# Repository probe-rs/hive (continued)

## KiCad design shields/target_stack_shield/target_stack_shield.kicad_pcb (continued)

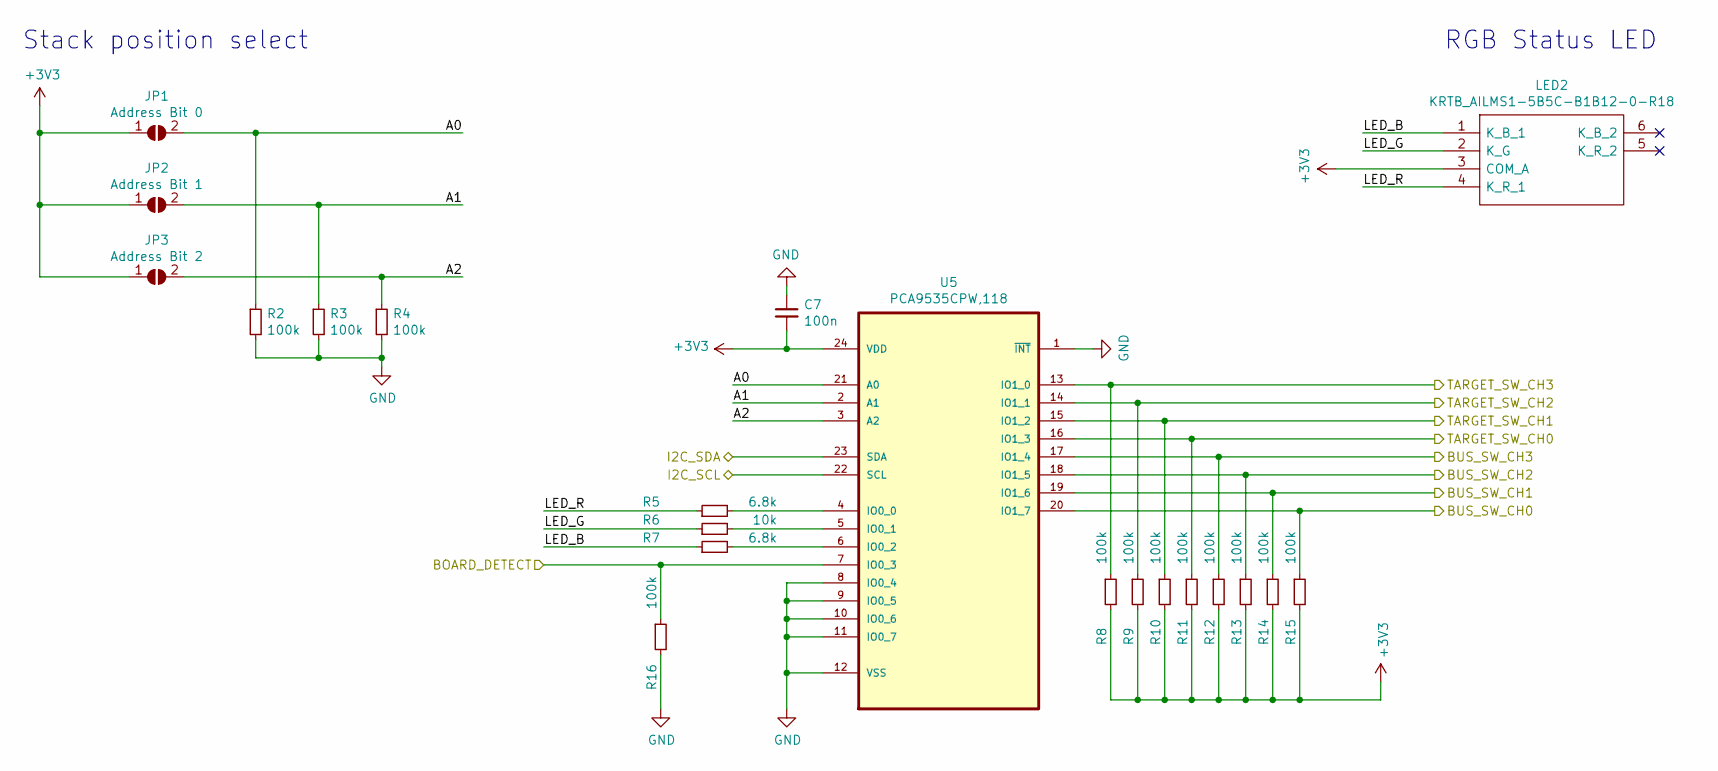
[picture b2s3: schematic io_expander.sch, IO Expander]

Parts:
C7: 100n; C_0603_1608Metric_Pad1.05x0.95mm_HandSolder
JP1: Address Bit 0; SolderJumper-2_P1.3mm_Open_TrianglePad1.0x1.5mm
JP2: Address Bit 1; SolderJumper-2_P1.3mm_Open_TrianglePad1.0x1.5mm
JP3: Address Bit 2; SolderJumper-2_P1.3mm_Open_TrianglePad1.0x1.5mm
LED2: KRTB_AILMS1-5B5C-B1B12-0-R18; KRTBAILMS15B5CB1B120R18; Mouser Part Number 720-KRTBAILMS1A2872
R2, R3, R4, R8, R9, R10, R11, R12, R13, R14, R15, R16: 100k; R_0603_1608Metric_Pad1.05x0.95mm_HandSolder
R5, R7: 6.8k; R_0603_1608Metric_Pad1.05x0.95mm_HandSolder
R6: 10k; R_0603_1608Metric_Pad1.05x0.95mm_HandSolder
U5: PCA9535CPW,118; SOP65P640X110-24N; MPN PCA9535CPW,118; Digikey Price (CHF) 1.9

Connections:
/BOARD_DETECT: R16.1, U5.7 (IO0_3); also elsewhere on the board
/Bus switches/BUS_SW_CH0: R15.1, U5.20 (IO1_7); also elsewhere on the board
/Bus switches/BUS_SW_CH1: R14.1, U5.19 (IO1_6); also elsewhere on the board
/Bus switches/BUS_SW_CH2: R13.1, U5.18 (IO1_5); also elsewhere on the board
/Bus switches/BUS_SW_CH3: R12.1, U5.17 (IO1_4); also elsewhere on the board
/Bus switches/IO Expander/A0: JP1.2 (B), R2.1, U5.21 (A0)
/Bus switches/IO Expander/A1: JP2.2 (B), R3.1, U5.2 (A1)
/Bus switches/IO Expander/A2: JP3.2 (B), R4.1, U5.3 (A2)
/Bus switches/IO Expander/LED_B: LED2.1 (K_B_1), R7.1
/Bus switches/IO Expander/LED_G: LED2.2 (K_G), R6.1
/Bus switches/IO Expander/LED_R: LED2.4 (K_R_1), R5.1
/Bus switches/TARGET_SW_CH0: R11.1, U5.16 (IO1_3); also elsewhere on the board
/Bus switches/TARGET_SW_CH1: R10.1, U5.15 (IO1_2); also elsewhere on the board
/Bus switches/TARGET_SW_CH2: R9.1, U5.14 (IO1_1); also elsewhere on the board
/Bus switches/TARGET_SW_CH3: R8.1, U5.13 (IO1_0); also elsewhere on the board
/I2C_SCL: U5.22 (SCL); also elsewhere on the board
/I2C_SDA: U5.23 (SDA); also elsewhere on the board
GND: C7.1, R2.2, R3.2, R4.2, R16.2, U5.1 (~INT), U5.8 (IO0_4), U5.9 (IO0_5), U5.10 (IO0_6), U5.11 (IO0_7), U5.12 (VSS); also elsewhere on the board
unnamed: R5.2, U5.4 (IO0_0)
unnamed: R6.2, U5.5 (IO0_1)
unnamed: R7.2, U5.6 (IO0_2)

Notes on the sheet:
Stack position select
RGB Status LED

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
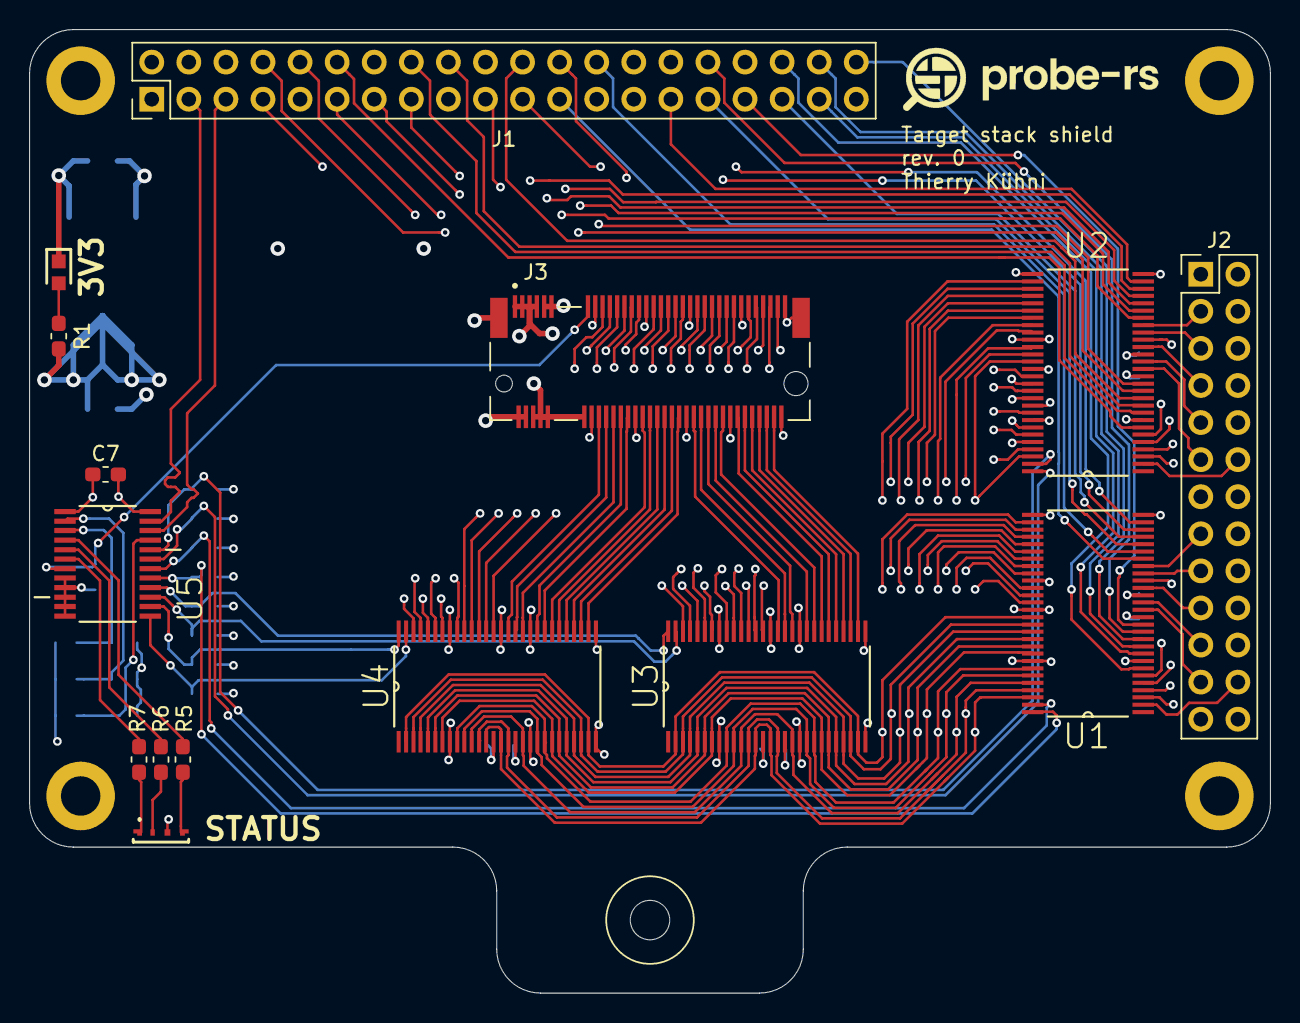
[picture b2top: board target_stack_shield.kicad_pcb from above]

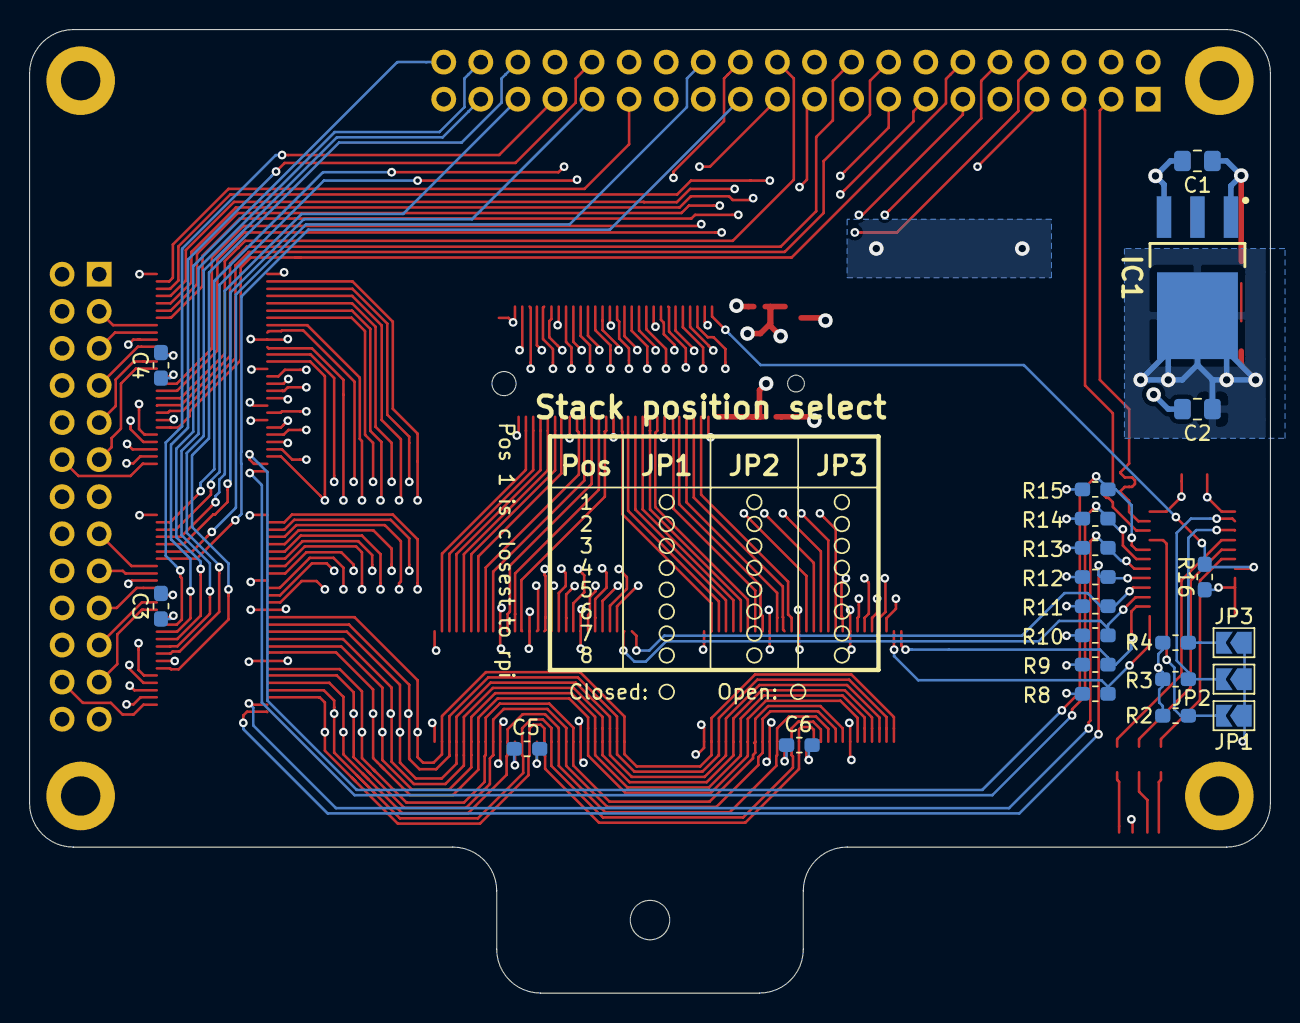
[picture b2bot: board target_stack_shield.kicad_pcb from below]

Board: 4 copper layers, 85.0 x 66.0 mm, 42 parts (22 on the bottom side), 123 nets.

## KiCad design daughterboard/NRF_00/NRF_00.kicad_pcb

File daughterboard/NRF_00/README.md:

## Daughterboard NRF_00
This Daughterboard features several nRF MCUs.

### Targets
The following targets are implemented on this Daughterboard:
| Designation | MCU |
| --- | --- |
| target0 | BT40E (nRF5340) |
| target1 | NRF52832-QFAB-T |
| target2 | NRF52840-DONGLE |
| target3 | NRF51822-QFAC-R7 |

### Partlist
The partlist for this Daughterboard is available [here](https://octopart.com/bom-tool/1QN2uwwk).

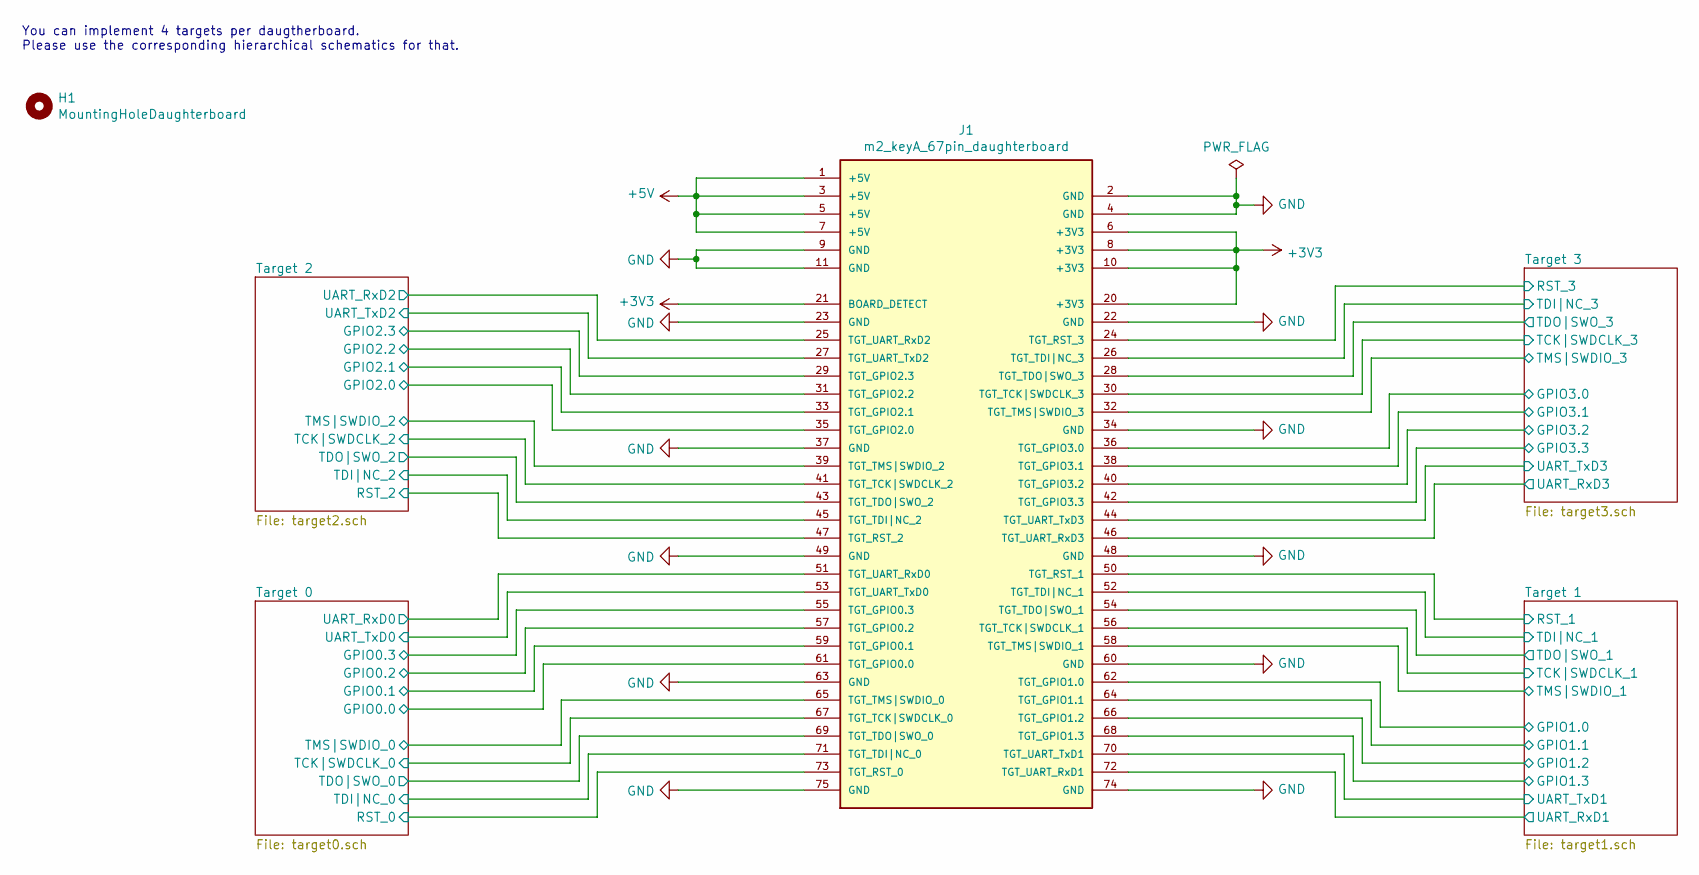
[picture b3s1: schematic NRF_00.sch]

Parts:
H1: MountingHoleDaughterboard; MountingHole_2.7mm_M2.5
J1: m2_keyA_67pin_daughterboard; m2_keyB

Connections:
+5V: J1.1 (+5V), J1.3 (+5V), J1.5 (+5V), J1.7 (+5V)
/Target 0/GPIO0.0: J1.61 (TGT_GPIO0.0); also elsewhere on the board
/Target 0/GPIO0.1: J1.59 (TGT_GPIO0.1); also elsewhere on the board
/Target 0/GPIO0.2: J1.57 (TGT_GPIO0.2); also elsewhere on the board
/Target 0/GPIO0.3: J1.55 (TGT_GPIO0.3); also elsewhere on the board
/Target 0/RST_0: J1.73 (TGT_RST_0); also elsewhere on the board
/Target 0/TCK|SWDCLK_0: J1.67 (TGT_TCK|SWDCLK_0); also elsewhere on the board
/Target 0/TDI|NC_0: J1.71 (TGT_TDI|NC_0); also elsewhere on the board
/Target 0/TDO|SWO_0: J1.69 (TGT_TDO|SWO_0); also elsewhere on the board
/Target 0/TMS|SWDIO_0: J1.65 (TGT_TMS|SWDIO_0); also elsewhere on the board
/Target 0/UART_RxD0: J1.51 (TGT_UART_RxD0); also elsewhere on the board
/Target 0/UART_TxD0: J1.53 (TGT_UART_TxD0); also elsewhere on the board
/Target 1/GPIO1.0: J1.62 (TGT_GPIO1.0); also elsewhere on the board
/Target 1/GPIO1.1: J1.64 (TGT_GPIO1.1); also elsewhere on the board
/Target 1/GPIO1.2: J1.66 (TGT_GPIO1.2); also elsewhere on the board
/Target 1/GPIO1.3: J1.68 (TGT_GPIO1.3); also elsewhere on the board
/Target 1/RST_1: J1.50 (TGT_RST_1); also elsewhere on the board
/Target 1/TCK|SWDCLK_1: J1.56 (TGT_TCK|SWDCLK_1); also elsewhere on the board
/Target 1/TDI|NC_1: J1.52 (TGT_TDI|NC_1); also elsewhere on the board
/Target 1/TDO|SWO_1: J1.54 (TGT_TDO|SWO_1); also elsewhere on the board
/Target 1/TMS|SWDIO_1: J1.58 (TGT_TMS|SWDIO_1); also elsewhere on the board
/Target 1/UART_RxD1: J1.72 (TGT_UART_RxD1); also elsewhere on the board
/Target 1/UART_TxD1: J1.70 (TGT_UART_TxD1); also elsewhere on the board
/Target 2/GPIO2.0: J1.35 (TGT_GPIO2.0); also elsewhere on the board
/Target 2/GPIO2.1: J1.33 (TGT_GPIO2.1); also elsewhere on the board
/Target 2/GPIO2.2: J1.31 (TGT_GPIO2.2); also elsewhere on the board
/Target 2/GPIO2.3: J1.29 (TGT_GPIO2.3); also elsewhere on the board
/Target 2/RST_2: J1.47 (TGT_RST_2); also elsewhere on the board
/Target 2/TCK|SWDCLK_2: J1.41 (TGT_TCK|SWDCLK_2); also elsewhere on the board
/Target 2/TDI|NC_2: J1.45 (TGT_TDI|NC_2); also elsewhere on the board
/Target 2/TDO|SWO_2: J1.43 (TGT_TDO|SWO_2); also elsewhere on the board
/Target 2/TMS|SWDIO_2: J1.39 (TGT_TMS|SWDIO_2); also elsewhere on the board
/Target 2/UART_RxD2: J1.25 (TGT_UART_RxD2); also elsewhere on the board
/Target 2/UART_TxD2: J1.27 (TGT_UART_TxD2); also elsewhere on the board
/Target 3/GPIO3.0: J1.36 (TGT_GPIO3.0); also elsewhere on the board
/Target 3/GPIO3.1: J1.38 (TGT_GPIO3.1); also elsewhere on the board
/Target 3/GPIO3.2: J1.40 (TGT_GPIO3.2); also elsewhere on the board
/Target 3/GPIO3.3: J1.42 (TGT_GPIO3.3); also elsewhere on the board
/Target 3/RST_3: J1.24 (TGT_RST_3); also elsewhere on the board
/Target 3/TCK|SWDCLK_3: J1.30 (TGT_TCK|SWDCLK_3); also elsewhere on the board
/Target 3/TDI|NC_3: J1.26 (TGT_TDI|NC_3); also elsewhere on the board
/Target 3/TDO|SWO_3: J1.28 (TGT_TDO|SWO_3); also elsewhere on the board
/Target 3/TMS|SWDIO_3: J1.32 (TGT_TMS|SWDIO_3); also elsewhere on the board
/Target 3/UART_RxD3: J1.46 (TGT_UART_RxD3); also elsewhere on the board
/Target 3/UART_TxD3: J1.44 (TGT_UART_TxD3); also elsewhere on the board
GND: J1.2 (GND), J1.4 (GND), J1.9 (GND), J1.11 (GND), J1.22 (GND), J1.23 (GND), J1.34 (GND), J1.37 (GND), J1.48 (GND), J1.49 (GND), J1.60 (GND), J1.63 (GND), J1.74 (GND), J1.75 (GND); also elsewhere on the board

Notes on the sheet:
You can implement 4 targets per daugtherboard. Please use the corresponding hierarchical schematics for that.

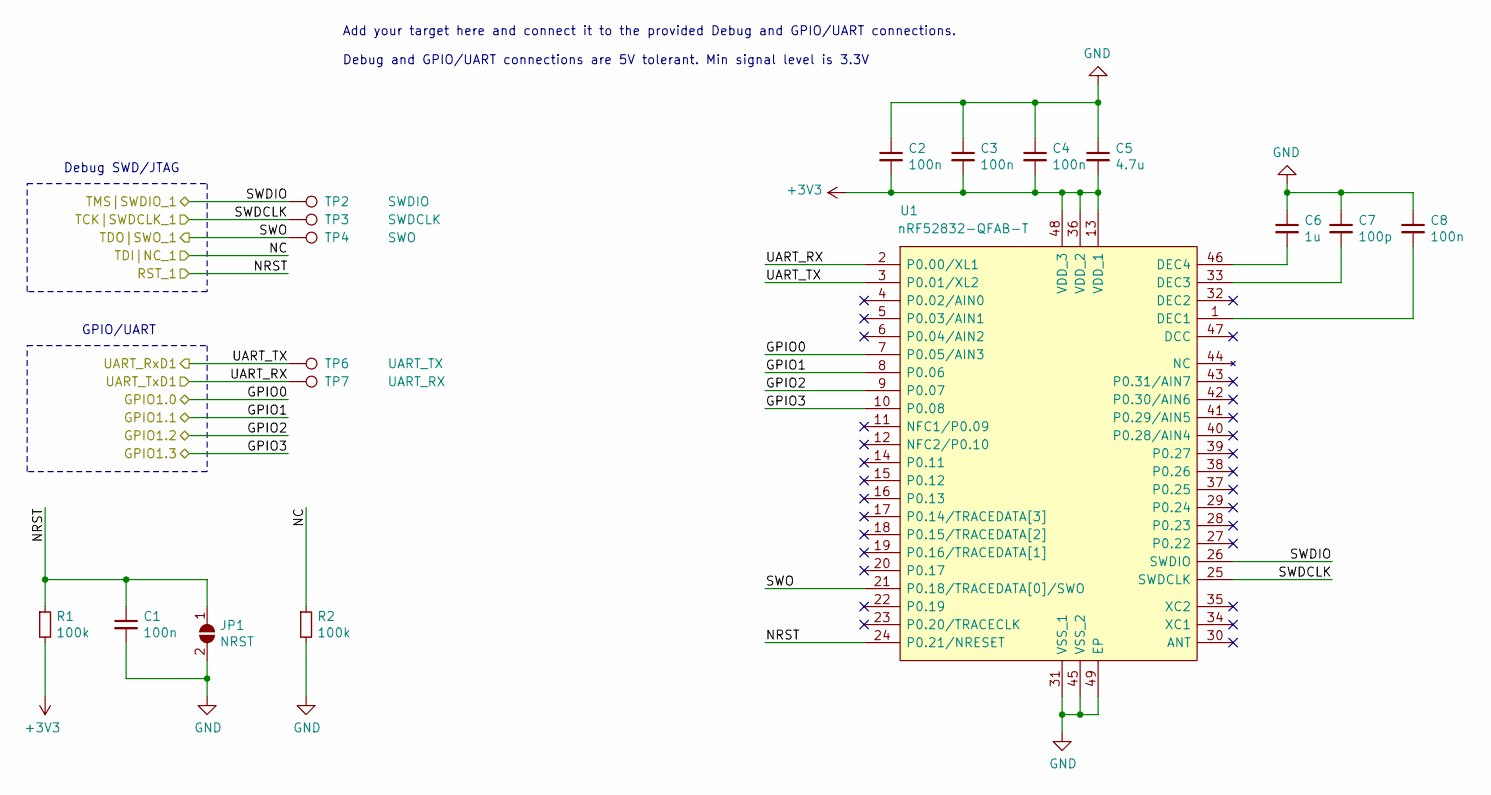
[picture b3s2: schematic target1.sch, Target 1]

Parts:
C1, C2, C3, C4, C8: 100n; C_0603_1608Metric_Pad1.05x0.95mm_HandSolder
C5: 4.7u; C_0603_1608Metric_Pad1.05x0.95mm_HandSolder
C6: 1u; C_0603_1608Metric_Pad1.05x0.95mm_HandSolder
C7: 100p; C_0603_1608Metric_Pad1.05x0.95mm_HandSolder
JP1: NRST; SolderJumper-2_P1.3mm_Open_TrianglePad1.0x1.5mm
R1, R2: 100k; R_0603_1608Metric_Pad1.05x0.95mm_HandSolder
TP2: SWDIO; TestPoint_Pad_1.0x1.0mm
TP3: SWDCLK; TestPoint_Pad_1.0x1.0mm
TP4: SWO; TestPoint_Pad_1.0x1.0mm
TP6: UART_TX; TestPoint_Pad_1.0x1.0mm
TP7: UART_RX; TestPoint_Pad_1.0x1.0mm
U1: nRF52832-QFAB-T; Mouser Part Number 949-NRF52832-QFAB-T

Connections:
/Target 1/GPIO1.0: U1.7 (P0.05/AIN3); also elsewhere on the board
/Target 1/GPIO1.1: U1.8 (P0.06); also elsewhere on the board
/Target 1/GPIO1.2: U1.9 (P0.07); also elsewhere on the board
/Target 1/GPIO1.3: U1.10 (P0.08); also elsewhere on the board
/Target 1/RST_1: C1.1, JP1.1 (A), R1.1, U1.24 (P0.21/NRESET); also elsewhere on the board
/Target 1/TCK|SWDCLK_1: TP3.1, U1.25 (SWDCLK); also elsewhere on the board
/Target 1/TDI|NC_1: R2.1; also elsewhere on the board
/Target 1/TDO|SWO_1: TP4.1, U1.21 (P0.18/TRACEDATA[0]/SWO); also elsewhere on the board
/Target 1/TMS|SWDIO_1: TP2.1, U1.26 (SWDIO); also elsewhere on the board
/Target 1/UART_RxD1: TP6.1, U1.3 (P0.01/XL2); also elsewhere on the board
/Target 1/UART_TxD1: TP7.1, U1.2 (P0.00/XL1); also elsewhere on the board
GND: C1.2, C2.1, C3.1, C4.1, C5.1, C6.1, C7.1, C8.1, JP1.2 (B), R2.2, U1.31 (VSS_1), U1.45 (VSS_2), U1.49 (EP); also elsewhere on the board
unnamed: C6.2, U1.46 (DEC4)
unnamed: C7.2, U1.33 (DEC3)
unnamed: C8.2, U1.1 (DEC1)

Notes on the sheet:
Debug SWD/JTAG
GPIO/UART
Add your target here and connect it to the provided Debug and GPIO/UART connections. Debug and GPIO/UART connections are 5V tolerant. Min signal level is 3.3V

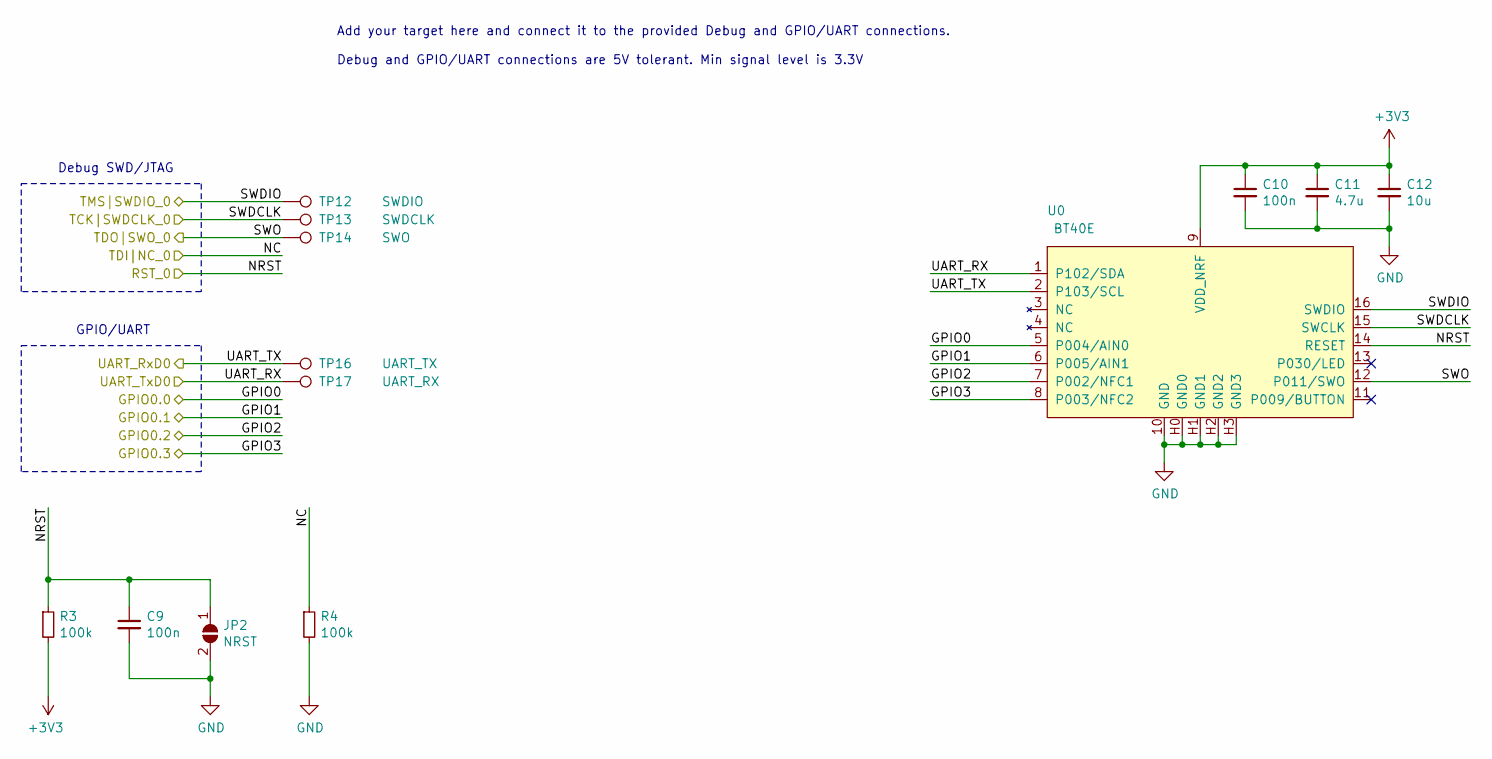
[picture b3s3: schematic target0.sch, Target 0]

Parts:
C9, C10: 100n; C_0603_1608Metric_Pad1.05x0.95mm_HandSolder
C11: 4.7u; C_0603_1608Metric_Pad1.05x0.95mm_HandSolder
C12: 10u; C_0603_1608Metric_Pad1.05x0.95mm_HandSolder
JP2: NRST; SolderJumper-2_P1.3mm_Open_TrianglePad1.0x1.5mm
R3, R4: 100k; R_0603_1608Metric_Pad1.05x0.95mm_HandSolder
TP12: SWDIO; TestPoint_Pad_1.0x1.0mm
TP13: SWDCLK; TestPoint_Pad_1.0x1.0mm
TP14: SWO; TestPoint_Pad_1.0x1.0mm
TP16: UART_TX; TestPoint_Pad_1.0x1.0mm
TP17: UART_RX; TestPoint_Pad_1.0x1.0mm
U0: BT40E

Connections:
/Target 0/GPIO0.0: U0.5 (P004/AIN0); also elsewhere on the board
/Target 0/GPIO0.1: U0.6 (P005/AIN1); also elsewhere on the board
/Target 0/GPIO0.2: U0.7 (P002/NFC1); also elsewhere on the board
/Target 0/GPIO0.3: U0.8 (P003/NFC2); also elsewhere on the board
/Target 0/RST_0: C9.1, JP2.1 (A), R3.1, U0.14 (RESET); also elsewhere on the board
/Target 0/TCK|SWDCLK_0: TP13.1, U0.15 (SWCLK); also elsewhere on the board
/Target 0/TDI|NC_0: R4.1; also elsewhere on the board
/Target 0/TDO|SWO_0: TP14.1, U0.12 (P011/SWO); also elsewhere on the board
/Target 0/TMS|SWDIO_0: TP12.1, U0.16 (SWDIO); also elsewhere on the board
/Target 0/UART_RxD0: TP16.1, U0.2 (P103/SCL); also elsewhere on the board
/Target 0/UART_TxD0: TP17.1, U0.1 (P102/SDA); also elsewhere on the board
GND: C9.2, C10.2, C11.2, C12.2, JP2.2 (B), R4.2, U0.10 (GND), U0.H0 (GND0), U0.H1 (GND1), U0.H2 (GND2), U0.H3 (GND3); also elsewhere on the board

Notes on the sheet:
Debug SWD/JTAG
GPIO/UART
Add your target here and connect it to the provided Debug and GPIO/UART connections. Debug and GPIO/UART connections are 5V tolerant. Min signal level is 3.3V

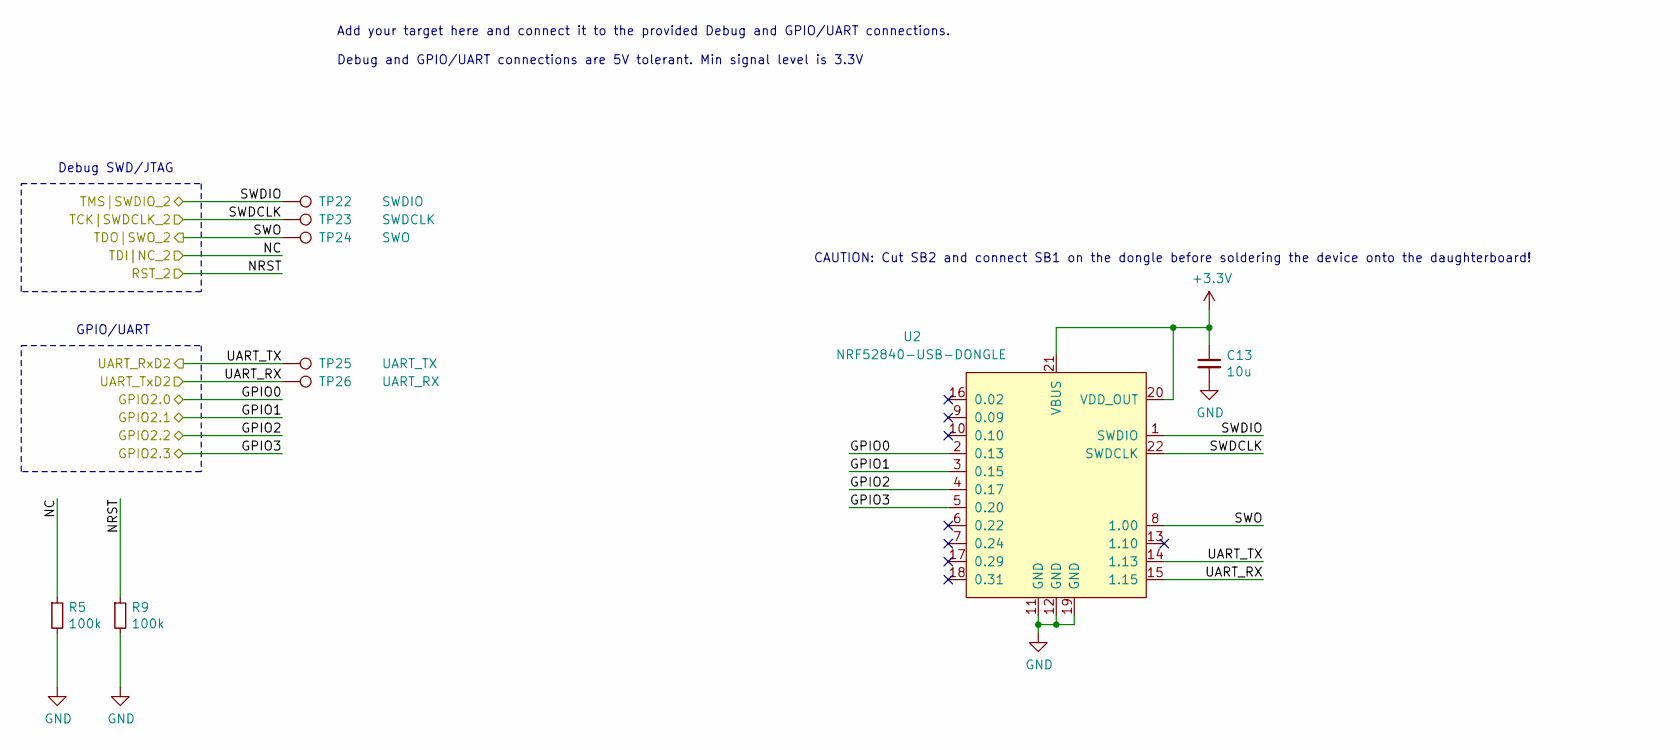
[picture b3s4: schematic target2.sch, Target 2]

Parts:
C13: 10u; C_0603_1608Metric_Pad1.05x0.95mm_HandSolder
R5, R9: 100k; R_0603_1608Metric_Pad1.05x0.95mm_HandSolder
TP22: SWDIO; TestPoint_Pad_1.0x1.0mm
TP23: SWDCLK; TestPoint_Pad_1.0x1.0mm
TP24: SWO; TestPoint_Pad_1.0x1.0mm
TP25: UART_TX; TestPoint_Pad_1.0x1.0mm
TP26: UART_RX; TestPoint_Pad_1.0x1.0mm
U2: NRF52840-USB-DONGLE

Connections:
/Target 2/GPIO2.0: U2.2 (0.13); also elsewhere on the board
/Target 2/GPIO2.1: U2.3 (0.15); also elsewhere on the board
/Target 2/GPIO2.2: U2.4 (0.17); also elsewhere on the board
/Target 2/GPIO2.3: U2.5 (0.20); also elsewhere on the board
/Target 2/RST_2: R9.1; also elsewhere on the board
/Target 2/TCK|SWDCLK_2: TP23.1, U2.22 (SWDCLK); also elsewhere on the board
/Target 2/TDI|NC_2: R5.1; also elsewhere on the board
/Target 2/TDO|SWO_2: TP24.1, U2.8 (1.00); also elsewhere on the board
/Target 2/TMS|SWDIO_2: TP22.1, U2.1 (SWDIO); also elsewhere on the board
/Target 2/UART_RxD2: TP25.1, U2.14 (1.13); also elsewhere on the board
/Target 2/UART_TxD2: TP26.1, U2.15 (1.15); also elsewhere on the board
GND: C13.2, R5.2, R9.2, U2.11 (GND), U2.12 (GND), U2.19 (GND); also elsewhere on the board

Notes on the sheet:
Debug SWD/JTAG
GPIO/UART
Add your target here and connect it to the provided Debug and GPIO/UART connections. Debug and GPIO/UART connections are 5V tolerant. Min signal level is 3.3V
CAUTION: Cut SB2 and connect SB1 on the dongle before soldering the device onto the daughterboard!

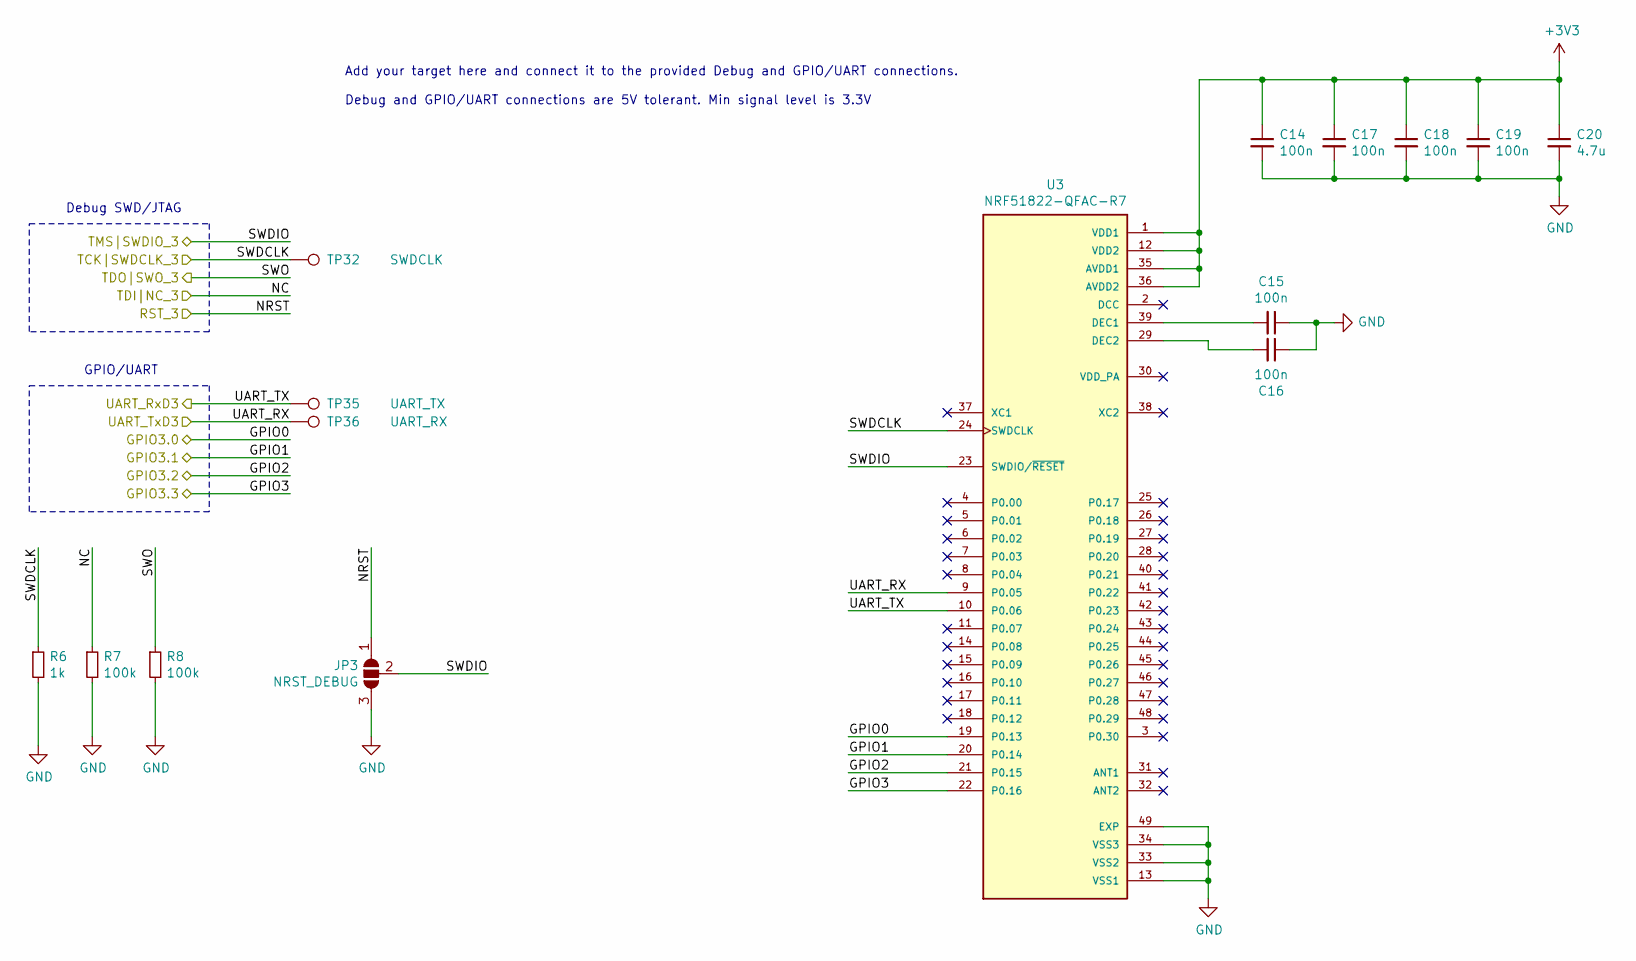
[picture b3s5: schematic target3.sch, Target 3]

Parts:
C14, C15, C16, C17, C18, C19: 100n; C_0603_1608Metric_Pad1.05x0.95mm_HandSolder
C20: 4.7u; C_0603_1608Metric_Pad1.05x0.95mm_HandSolder
JP3: NRST_DEBUG; SolderJumper-3_P2.0mm_Open_TrianglePad1.0x1.5mm_NumberLabels
R6: 1k; R_0603_1608Metric_Pad1.05x0.95mm_HandSolder
R7, R8: 100k; R_0603_1608Metric_Pad1.05x0.95mm_HandSolder
TP32: SWDCLK; TestPoint_Pad_1.0x1.0mm
TP35: UART_TX; TestPoint_Pad_1.0x1.0mm
TP36: UART_RX; TestPoint_Pad_1.0x1.0mm
U3: NRF51822-QFAC-R7

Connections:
/Target 3/GPIO3.0: U3.19 (P0.13); also elsewhere on the board
/Target 3/GPIO3.1: U3.20 (P0.14); also elsewhere on the board
/Target 3/GPIO3.2: U3.21 (P0.15); also elsewhere on the board
/Target 3/GPIO3.3: U3.22 (P0.16); also elsewhere on the board
/Target 3/RST_3: JP3.1 (A); also elsewhere on the board
/Target 3/TCK|SWDCLK_3: R6.1, TP32.1, U3.24 (SWDCLK); also elsewhere on the board
/Target 3/TDI|NC_3: R7.1; also elsewhere on the board
/Target 3/TDO|SWO_3: R8.1; also elsewhere on the board
/Target 3/TMS|SWDIO_3: JP3.2 (C), U3.23 (SWDIO/~RESET); also elsewhere on the board
/Target 3/UART_RxD3: TP35.1, U3.10 (P0.06); also elsewhere on the board
/Target 3/UART_TxD3: TP36.1, U3.9 (P0.05); also elsewhere on the board
GND: C14.2, C15.1, C16.1, C17.2, C18.2, C19.2, C20.2, JP3.3 (B), R6.2, R7.2, R8.2, U3.13 (VSS1), U3.33 (VSS2), U3.34 (VSS3), U3.49 (EXP); also elsewhere on the board
unnamed: C15.2, U3.39 (DEC1)
unnamed: C16.2, U3.29 (DEC2)

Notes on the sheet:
Debug SWD/JTAG
GPIO/UART
Add your target here and connect it to the provided Debug and GPIO/UART connections. Debug and GPIO/UART connections are 5V tolerant. Min signal level is 3.3V

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
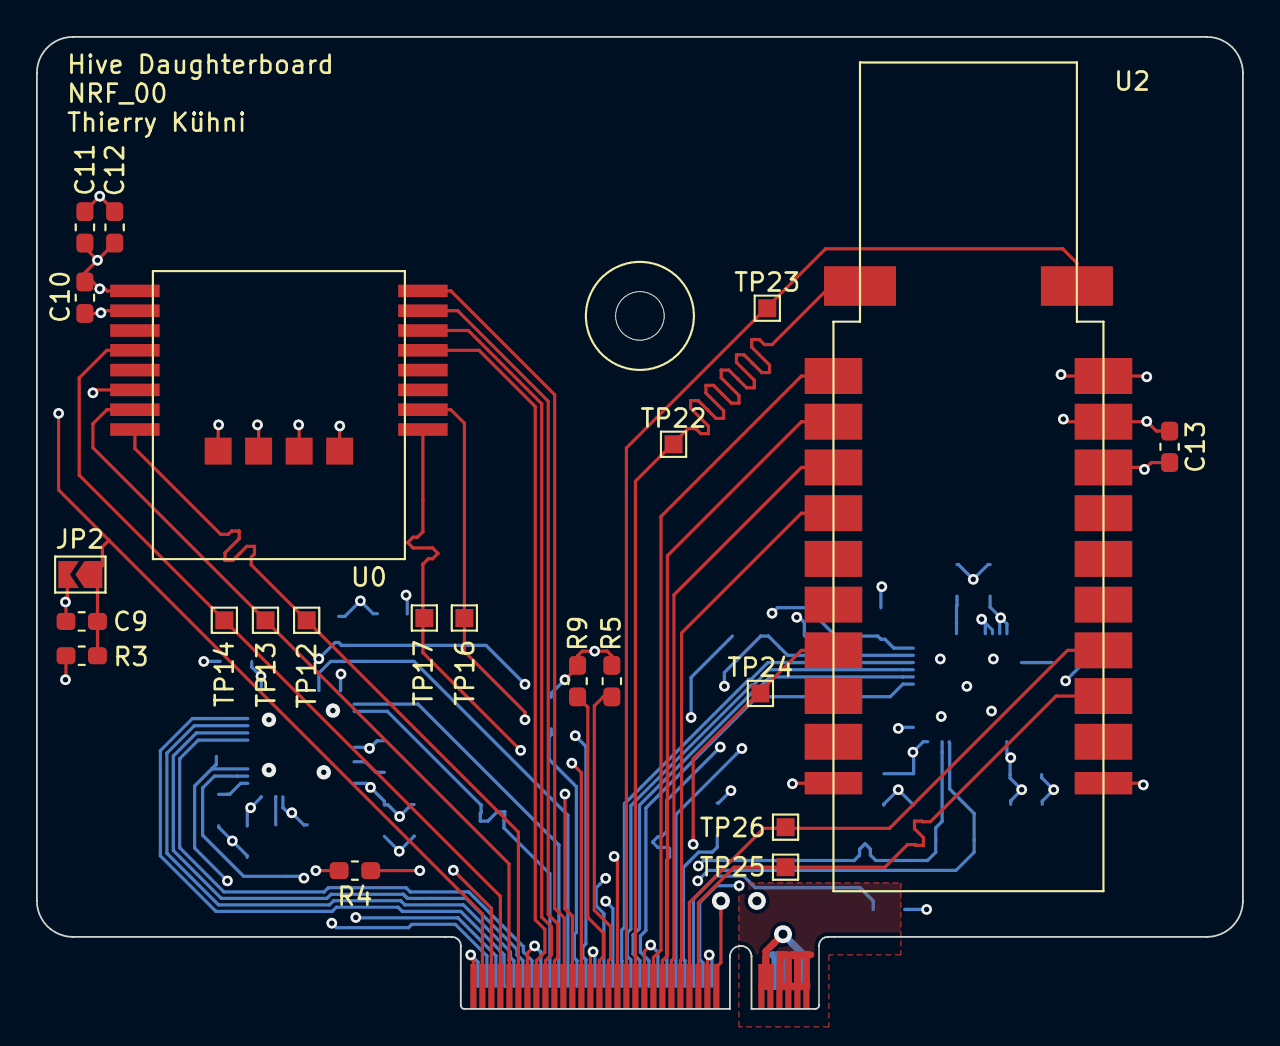
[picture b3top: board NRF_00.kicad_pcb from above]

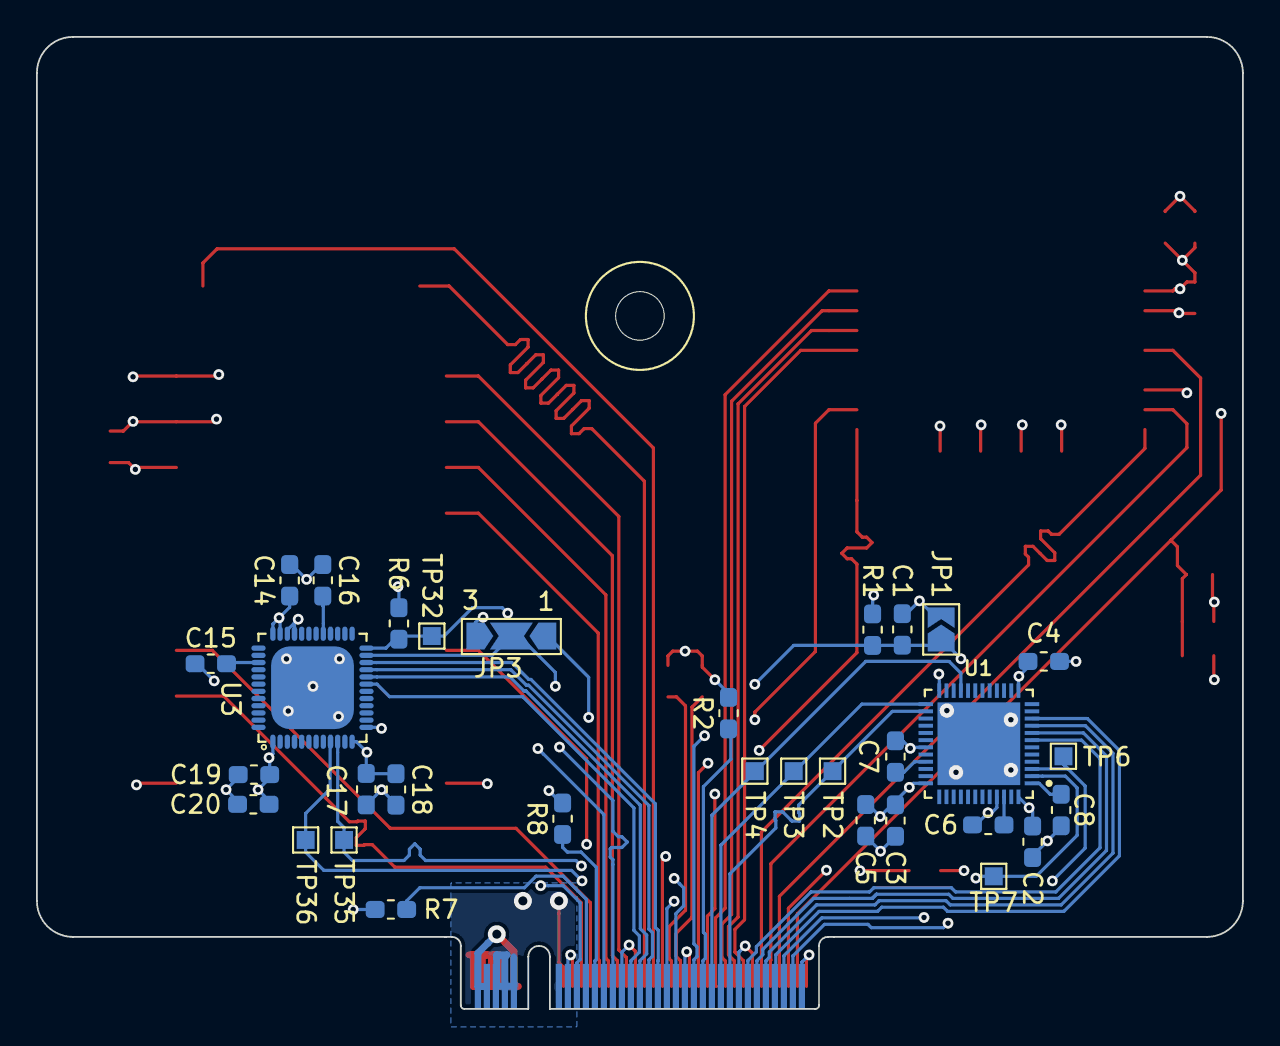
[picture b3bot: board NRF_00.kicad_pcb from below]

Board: 4 copper layers, 67.0 x 54.0 mm, 56 parts (32 on the bottom side), 52 nets.
